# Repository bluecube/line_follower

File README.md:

Line follower v2
================

This is a robot I made to tinker with and to compete in the [Robotic Day](https://roboticday.org/) competition. (Actually the original goal was Robotic Day 2016, but stuff got delayed :) )

The design is an attempt to make a line follower with minimum effort on the hardware side and maximum versatility on the software side.

The robot body consists of a 8cm x 10cm double sided PCB, two geared N20 DC encoder motors with Pololu wheels and magnetic encoders and a few 3D printed bits.
The most important electronic components are ESP32 development board for computing power and line sensor inspired by [Ondřej Staněk's PocketBot](http://www.ostan.cz/pocketBot/), as a bonus the robot also carries an IR range sensor and MPU 6050 breakout board (accelerometer and gyro).

This repository should contain everything necessary to build and run the robot in the competition.
Let me know if you decide to build it!

This is a v2, you can also check out the [v1](https://github.com/bluecube/line_follower/tree/v1/).

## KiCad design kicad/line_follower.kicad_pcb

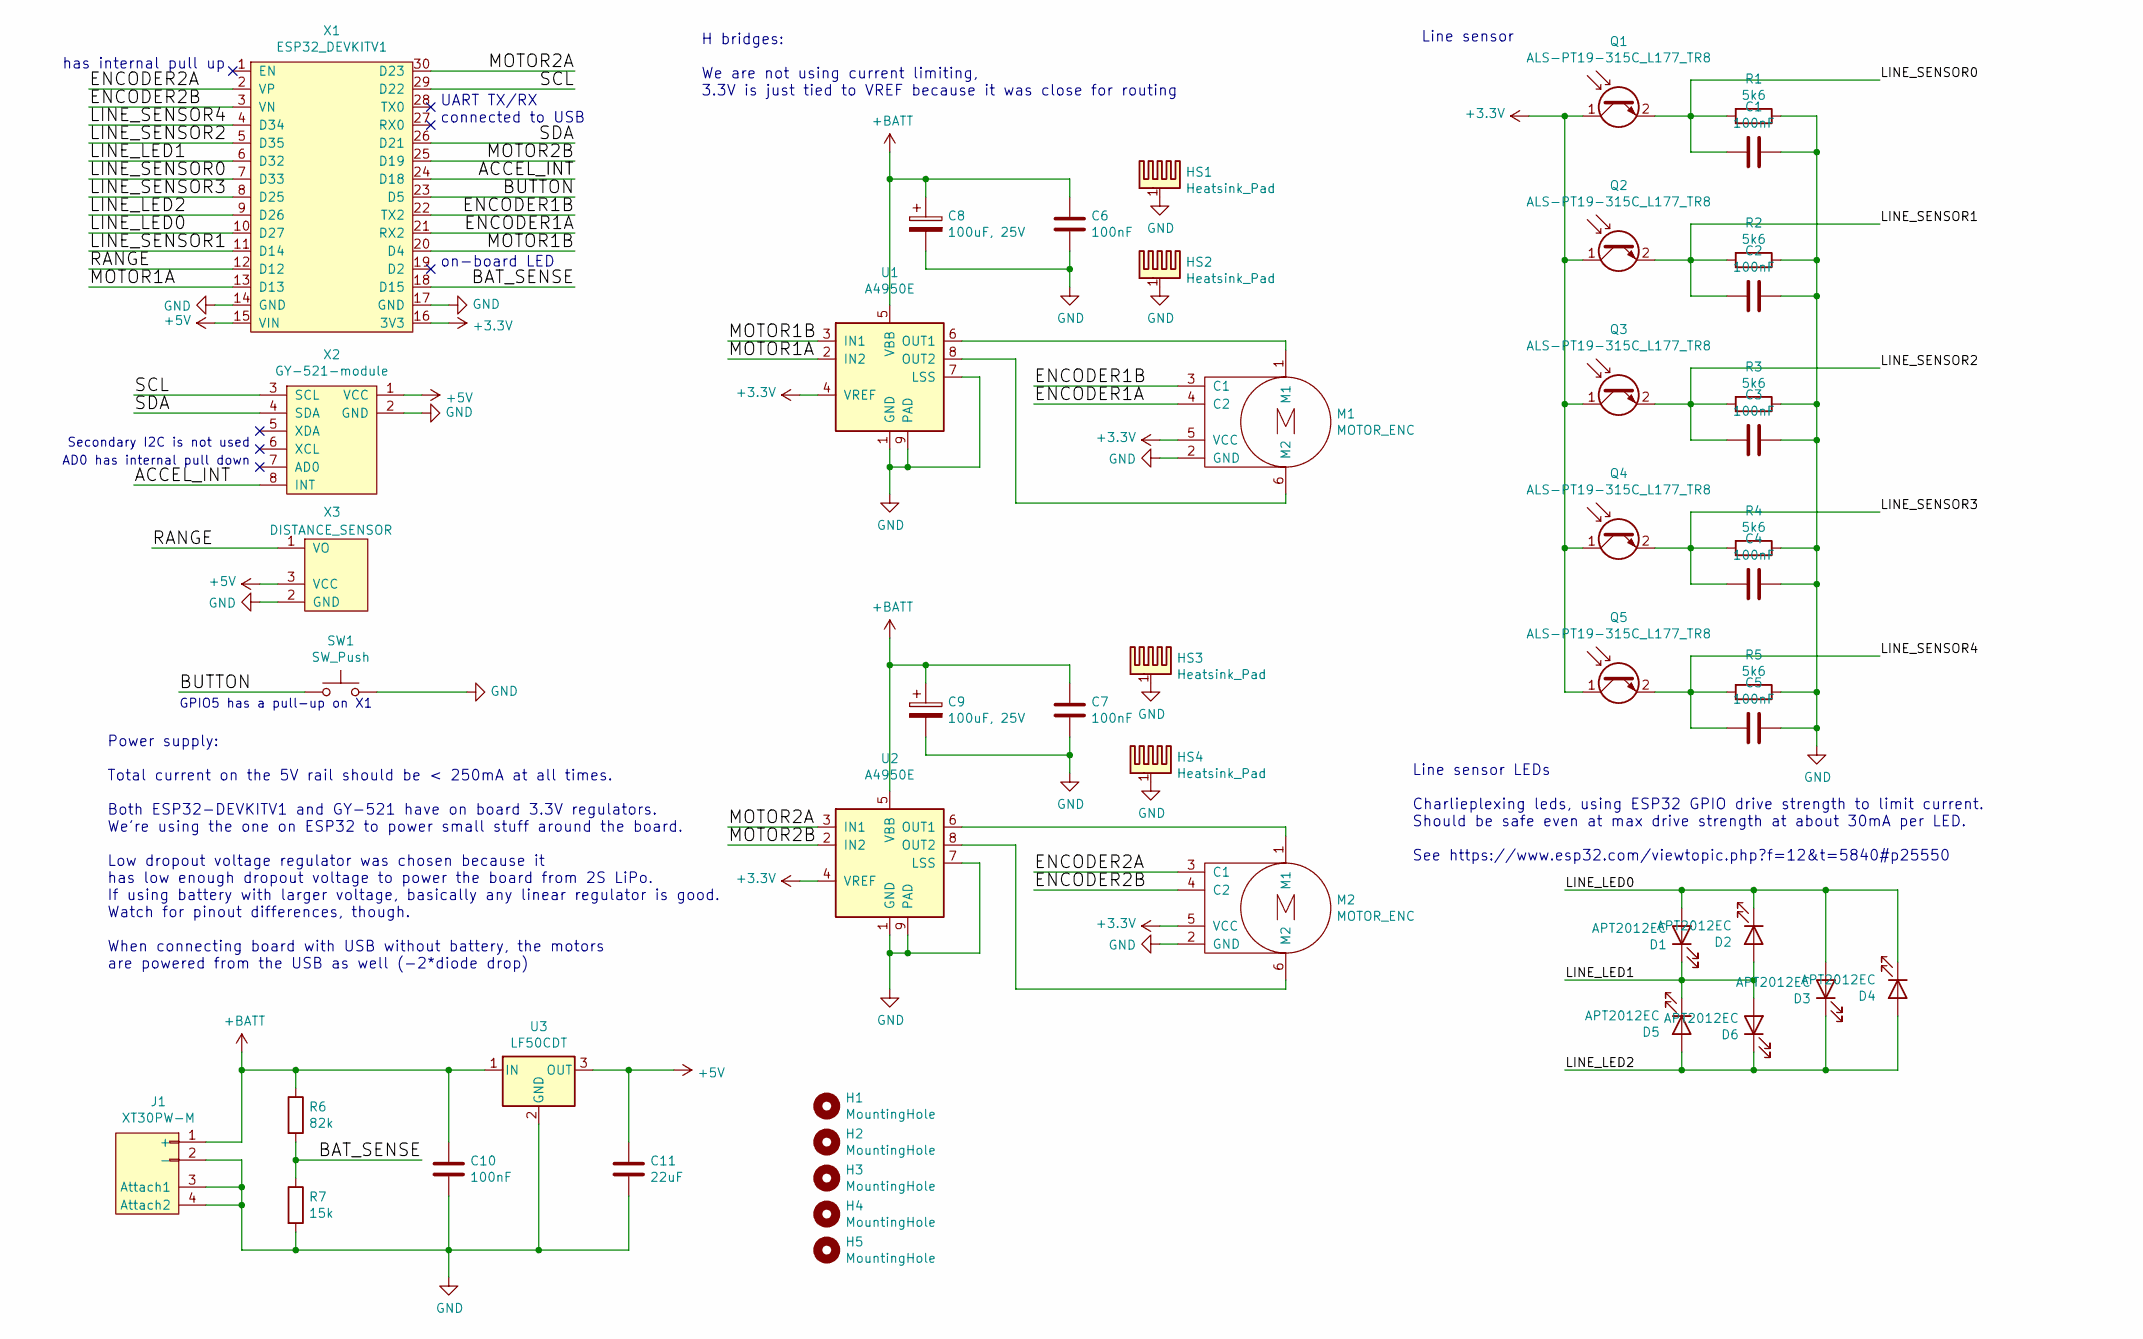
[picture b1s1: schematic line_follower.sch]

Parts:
C1, C2, C3, C4, C5, C6, C7, C10: 100nF; C_0805_2012Metric_Pad1.15x1.40mm_HandSolder
C8, C9: 100uF, 25V; CP_Elec_6.3x5.8
C11: 22uF; C_0805_2012Metric_Pad1.15x1.40mm_HandSolder
D1, D2, D3, D4, D5, D6: APT2012EC; LED_0805_2012Metric_Pad1.15x1.40mm_HandSolder
H1, H2, H3, H4, H5: MountingHole; MountingHole_3.2mm_M3
HS1, HS2, HS3, HS4: Heatsink_Pad; 3x3_thermal_vias
J1: XT30PW-M
M1, M2: MOTOR_ENC; SolderWirePad2x3_p2.54_staggered
Q1, Q2, Q3, Q4, Q5: ALS-PT19-315C_L177_TR8; phototransistor-1.7mm
R1, R2, R3, R4, R5: 5k6; R_0805_2012Metric_Pad1.15x1.40mm_HandSolder
R6: 82k; R_0805_2012Metric_Pad1.15x1.40mm_HandSolder
R7: 15k; R_0805_2012Metric_Pad1.15x1.40mm_HandSolder
SW1: SW_Push; 4.5mm_tact_switch
U1, U2: A4950E; SOIC-8-1EP_3.9x4.9mm_P1.27mm_EP2.41x3.3mm_HandSolder
U3: LF50CDT; TO-252-2
X1: ESP32_DEVKITV1
X2: GY-521-module
X3: DISTANCE_SENSOR; SolderWirePad1x3_p2.54

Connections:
+3V3: M1.5 (VCC), M2.5 (VCC), Q1.1 (C), Q2.1 (C), Q3.1 (C), Q4.1 (C), Q5.1 (C), U1.4 (VREF), U2.4 (VREF), X1.16 (3V3)
+5V: C11.1, U3.3 (OUT), X1.15 (VIN), X2.1 (VCC), X3.3 (VCC)
+BATT: C6.1, C7.1, C8.1, C9.1, C10.1, J1.1 (+), R6.1, U1.5 (VBB), U2.5 (VBB), U3.1 (IN)
/ACCEL_INT: X1.24 (D18), X2.8 (INT)
/BAT_SENSE: R6.2, R7.1, X1.18 (D15)
/BUTTON: SW1.1, X1.23 (D5)
/ENCODER1A: M1.4 (C2), X1.21 (RX2)
/ENCODER1B: M1.3 (C1), X1.22 (TX2)
/ENCODER2A: M2.3 (C1), X1.2 (VP)
/ENCODER2B: M2.4 (C2), X1.3 (VN)
/LINE_LED0: D1.2 (A), D2.1 (K), D3.2 (A), D4.1 (K), X1.10 (D27)
/LINE_LED1: D1.1 (K), D2.2 (A), D5.1 (K), D6.2 (A), X1.6 (D32)
/LINE_LED2: D3.1 (K), D4.2 (A), D5.2 (A), D6.1 (K), X1.9 (D26)
/LINE_SENSOR0: C1.2, Q1.2 (E), R1.2, X1.7 (D33)
/LINE_SENSOR1: C2.2, Q2.2 (E), R2.2, X1.11 (D14)
/LINE_SENSOR2: C3.2, Q3.2 (E), R3.2, X1.5 (D35)
/LINE_SENSOR3: C4.2, Q4.2 (E), R4.2, X1.8 (D25)
/LINE_SENSOR4: C5.2, Q5.2 (E), R5.2, X1.4 (D34)
/MOTOR1A: U1.2 (IN2), X1.13 (D13)
/MOTOR1B: U1.3 (IN1), X1.20 (D4)
/MOTOR2A: U2.3 (IN1), X1.30 (D23)
/MOTOR2B: U2.2 (IN2), X1.25 (D19)
/RANGE: X1.12 (D12), X3.1 (VO)
/SCL: X1.29 (D22), X2.3 (SCL)
/SDA: X1.26 (D21), X2.4 (SDA)
GND: C1.1, C2.1, C3.1, C4.1, C5.1, C6.2, C7.2, C8.2, C9.2, C10.2, C11.2, HS1.1, HS2.1, HS3.1, HS4.1, J1.2 (-), J1.3 (Attach1), J1.4 (Attach2), M1.2 (GND), M2.2 (GND), R1.1, R2.1, R3.1, R4.1, R5.1, R7.2, SW1.2, U1.1 (GND), U1.7 (LSS), U1.9 (PAD), U2.1 (GND), U2.7 (LSS), U2.9 (PAD), U3.2 (GND), X1.14 (GND), X1.17 (GND), X2.2 (GND), X3.2 (GND)
unnamed: M1.1 (M1), U1.6 (OUT1)
unnamed: M1.6 (M2), U1.8 (OUT2)
unnamed: M2.1 (M1), U2.6 (OUT1)
unnamed: M2.6 (M2), U2.8 (OUT2)

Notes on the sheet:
Power supply: Total current on the 5V rail should be < 250mA at all times. Both ESP32-DEVKITV1 and GY-521 have on board 3.3V regulators. We're using the one on ESP32 to power small stuff around the board. Low dropout voltage regulator was chosen because it has low enough dropout voltage to power th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
UART TX/RX connected to USB
on-board LED
AD0 has internal pull down
has internal pull up
Secondary I2C is not used
H bridges: We are not using current limiting, 3.3V is just tied to VREF because it was close for routing
Line sensor LEDs Charlieplexing leds, using ESP32 GPIO drive strength to limit current. Should be safe even at max drive strength at about 30mA per LED. See https://www.esp32.com/viewtopic.php?f=12&t=5840#p25550
Line sensor
GPIO5 has a pull-up on X1

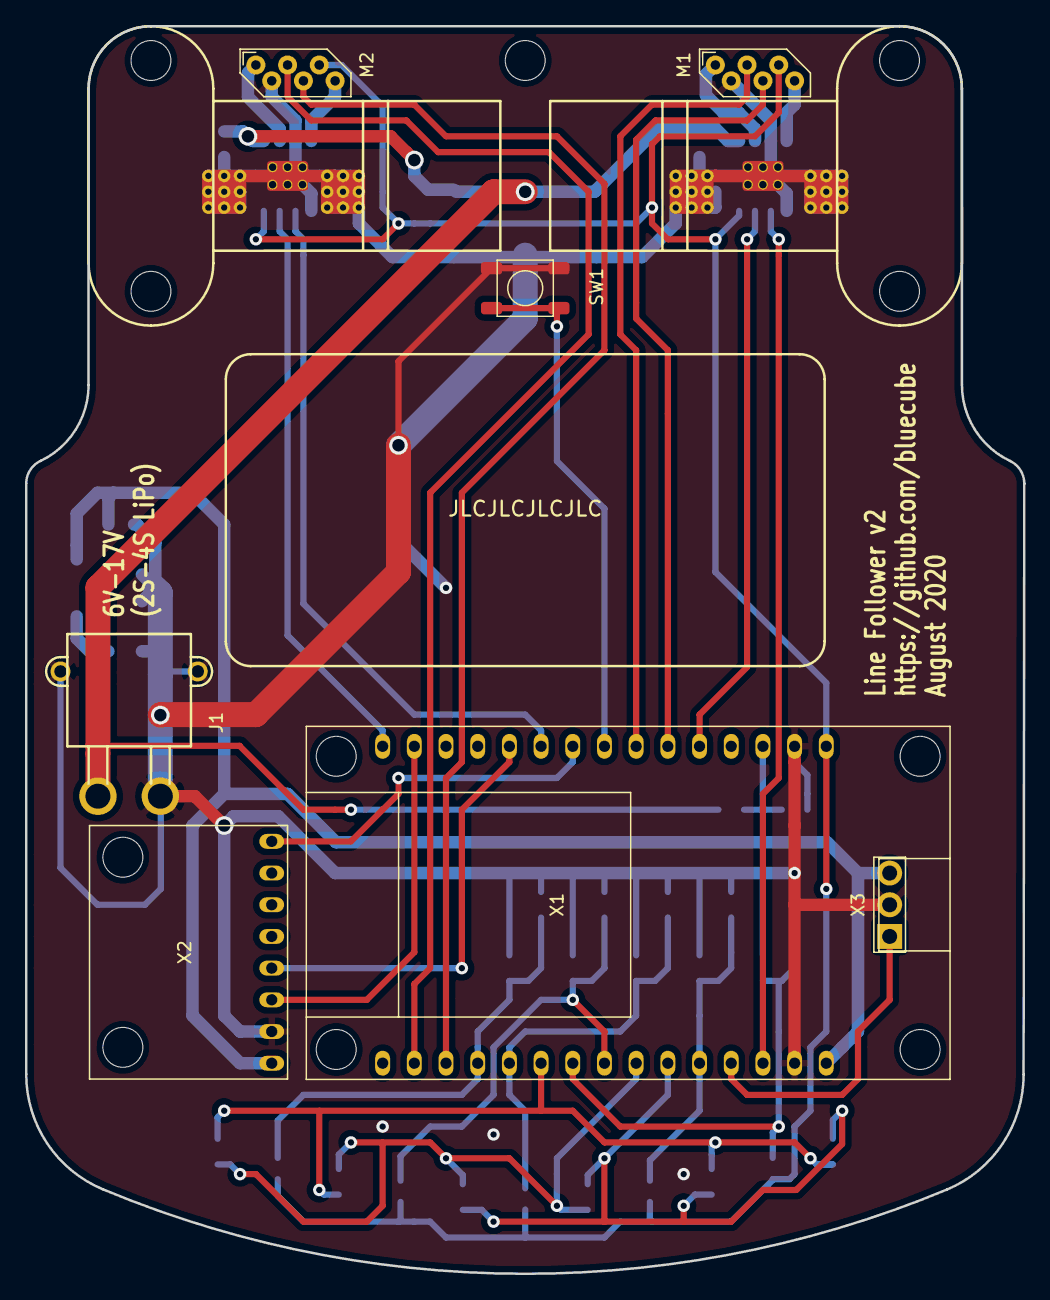
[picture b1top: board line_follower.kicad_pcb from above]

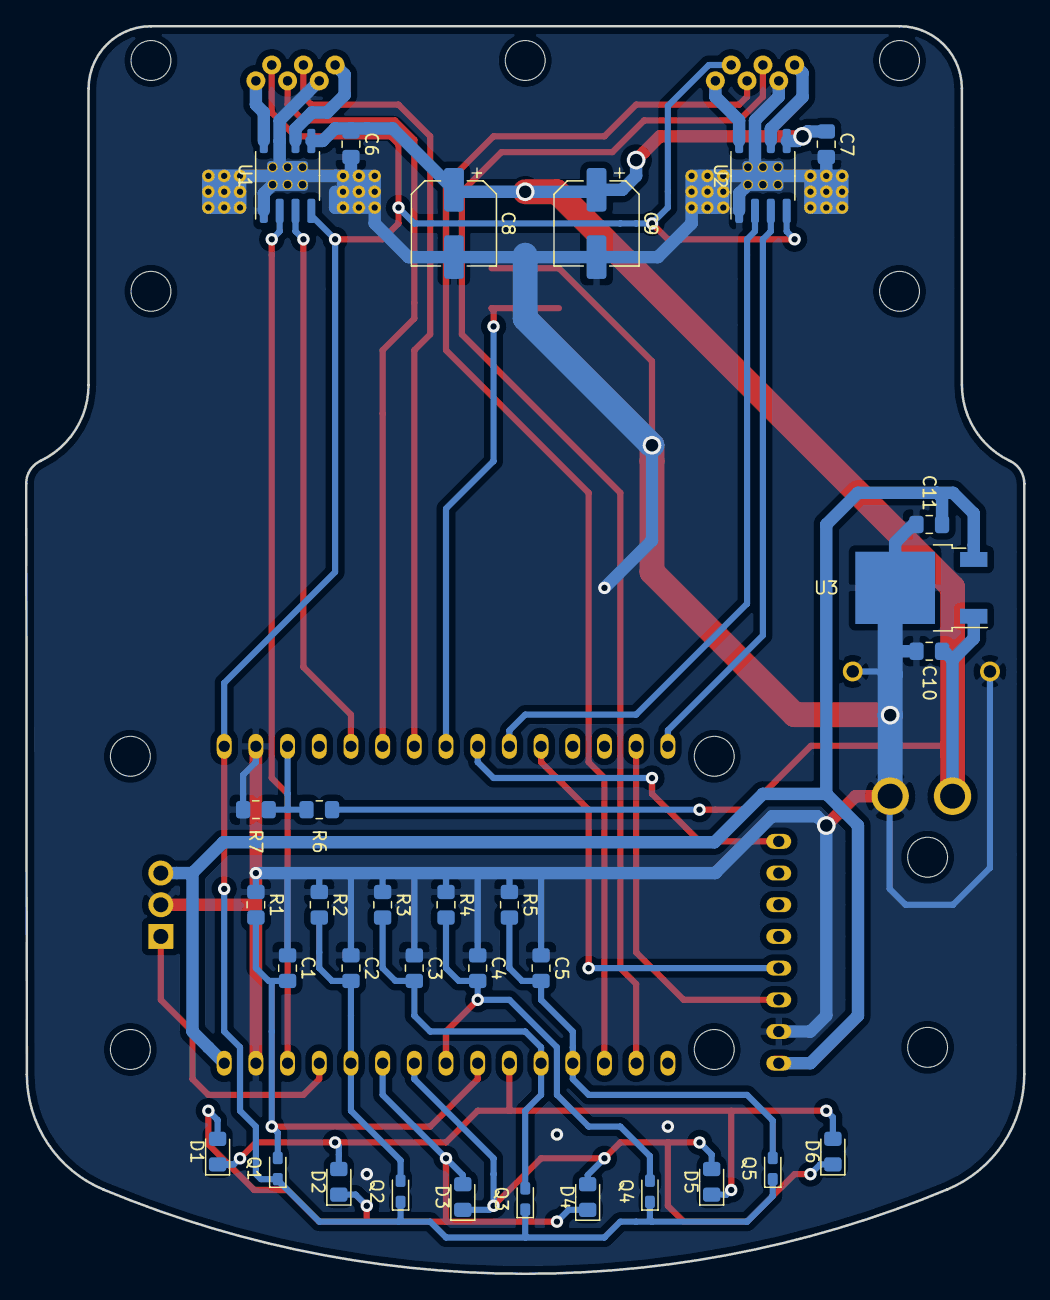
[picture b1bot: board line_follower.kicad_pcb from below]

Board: 2 copper layers, 80.0 x 100.0 mm, 48 parts (32 on the bottom side), 30 nets.

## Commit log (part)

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2016-04-03 Initial commit.
    3D sketch in solidworks and almost finished board.
2016-04-16 Fixes before sending the board for fab.
2016-05-12 Got rid of old versions of model.
2016-05-28 Testing arena design.
2016-05-29 Added missing connections to the board.
2016-06-27 Updated the testing map to 1x1.5m format.
2016-06-29 Updated testing map
2016-07-03 One more change of the testing map.
    I should really be doing more useful stuff :-)
2016-10-12 Blink zinc example that compiles
2016-10-12 Very rough (non compilable by far) idea of top level code separation
2017-02-13 More realistic wheel shape
2017-02-13 3D printable distance sensor bracket, front ball and motor brackets.
2017-02-13 Removed unused solidworks parts
2017-05-28 Working blink example
2018-12-16 Cleaned up old attempts
2019-01-06 Crosstool configuration for building the toolchain.
2019-01-06 Cleaning up the remaining pieces of rust coniguration.
2019-04-14 Starting with C++ project
2019-04-15 Larson scanner hello world with arduino.
2019-04-27 Settled on using Arduino with platformio.
2019-04-28 Playing with LEDs
2019-04-28 Added comment.
2019-04-28 Very simple reading of analog values.
2019-05-18 Carrying case first draft
2019-05-19 Short introduction text for Robotic Day 2019
2019-05-19 Robotic day photos.
2019-05-19 Fixed values of line sensor divider resistors.
2019-05-19 Started a list of hardware bugs.
2019-05-19 Some work done on the carrying box.
2019-05-19 Small change in robotic day introduction
2019-05-19 Readme improvements.
2019-05-20 Added a github link to short introduction file
2019-05-20 Create LICENSE
2019-05-21 Added jupyter notebook containing experiments with line detection cross-corelation kernels
2019-05-21 Line sensor reacts now.
2019-05-21 One more (minor) hardware bug.
2019-05-21 Prepared testing map for printing
2019-05-26 Carrying box ready for printing.
2019-05-26 Cleaning up line sensor code, using at least a few parallel ADC reads.
2019-05-27 Fixing uninitialized ADC instance after move to singleton.
2019-05-28 Line detection working.
2019-05-29 Simplified line detector.
2019-05-29 Renamed LfHal to RobotHal
2019-05-30 Debounced button input.
2019-05-31 Cleaning up Hal, simplified the replacability.
2019-06-01 Fixed changing motor directions (analogWrite and digitealWrite don't mix)
2019-06-01 State machine with basic line following code
2019-06-01 Added bootup state.
2019-06-01 Setting loop period
2019-06-01 Somehow working line following
2019-06-01 Fixing missing enum members in switch
2019-06-01 Rudimentary battery voltage monitoring
2019-06-01 Still fiddling with parameters
2019-06-02 Smoother line finding.
2020-04-25 Schematic for V2 mostly complete, time to work on the board.
2020-04-26 Removed obsolete solidworks models
2020-04-26 Updated gitignore
2020-04-26 You'll have to google for the datasheets yourself.
2020-04-26 Rough layout of the new board
2020-04-29 Modelled a bunch of new parts for the robot
2020-04-29 Decided to not use the encoder board on the motors, schematic tweaks and start of layout
2020-05-19 Motor encoder boards are back, more layout work
2020-05-20 Another quarter-afternoon of layout
2020-05-22 Everything is connected on the board, but more work remains
2020-05-22 Layout complete, now a day or two for it to sink in and find more errors.
2020-06-04 started working on kicad version of the board
2020-07-01 Board: Almost complete schematic, rough layout of pcb
2020-07-01 WIP mechanical design in F360
2020-07-23 Getting there with the PCB design.
2020-07-24 Updated sensor components position export
2020-08-02 Board done except for the motor mounts
2020-08-02 Small PCB tweaks
2020-08-02 Placed motor mounting holes and silkscreen outlines.
    Board done for now.
2020-08-09 Untangled routing at the front of the robot a bit, moved battery location
2020-08-10 board: A bit more tweaking
2020-08-10 board: Moving silkscreen labels
2020-08-13 board: Manually fixed the outline to make step exporter happy
2020-08-15 Ignoring kicad autosave files.
2020-08-15 mechanical: WIP 3d printed parts and robot layout
    Front top and bottom pieces are ready, motor mounts and deck are missing
2020-08-26 board: Added model for microswitch
2020-08-26 board: Some silkscreen change ...
2020-08-26 schematic: Fixing DRC warnings
2020-08-26 schematic: Removed comment
2020-08-26 board: Small tweaks + updating to match previous changes.
2020-08-26 board: Gerber files, sent for manufacture
2020-10-02 CAD model ready for 3D printing
2020-10-02 Added Step export of the CAD model
2020-10-06 mechanical: Updated based experimental prints.
2020-10-14 schematic: Modified power supply LDO because of availability at Mouser.
2020-10-14 mechanical: More updates, refreshed exports
2020-10-15 mechanical: Cleanup + added readme
2020-11-08 Set theme jekyll-theme-cayman
2020-11-12 Exporter script for the Fusion360 design
2020-11-12 schematic: Changed the 5V regulator again
    the previous one had wrong pinout
2020-11-12 mechanical: Printability improvements and smaller tweaks
2020-11-13 Renamed kicad exports directory
2020-12-06 Updated platformio to work with ESP32.
2020-12-06 Removed Arduino calls from code except HAL
2020-12-06 Silencing compiler warnings
2020-12-07 RobotHal: Got rid of Arduino remnants
2020-12-07 RobotHal: New pin assignments
2020-12-07 RobotHal: Singleton stuff
2020-12-07 Formating
2020-12-08 Using C++17
2020-12-08 Blinking LEDs through RobotHal
2020-12-10 Removed the obsolete eagle project
2020-12-10 Removed obsolete solidworks designs
2020-12-10 Updated README to reflect the branch renaming
2020-12-10 Fixed image path in readme
2020-12-10 Line sensor buffer definitions.
2020-12-12 Naming convention
2020-12-12 Got rid of time types for now (will be replaced by std::chrono later)
2020-12-12 WIP line sensor reading
2020-12-12 Line sensor kind of working
2020-12-20 Reading motor encoders
2020-12-20 Printf!
2020-12-22 Moved RobotHal to a separate directory
2020-12-22 Coding style change for encoder configuration
2020-12-23 idf_util needed to be moved as well
2020-12-23 Added Vector3D class
2020-12-25 Initial non-working IMU code
2020-12-26 Refactored Line sensor to a separate class under HAL
2020-12-26 IMU HAL component uses static methods rather than HAL reference.
2020-12-26 More reasonable naming scheme for HAL components
2020-12-26 Refactored motor control to separate HAL component
2020-12-26 Utility for checking ESP-IDF error codes
2020-12-26 Debug print tweaks
2020-12-27 HAL: Reading battery voltage
2020-12-27 Removed commented block of old code from main
2020-12-27 HAL: Line sensor LED pins should start as disabled
2020-12-27 HAL: Setting motor PWM
2020-12-27 HAL: Fixing I2C register reading code
2020-12-27 HAL: One more printf during init
2020-12-27 HAL/Mpu6050: Checking connection, attempting to wake from sleep mode
    Connection works, but accelerometer and gyro still read as zeros
2020-12-31 Removed old documentation related to v1
2020-12-31 Moved the line sensor experiments to jupyter directory
2021-01-03 Schematic of the planned balancing algorithm.
2021-01-08 HAL: Motor beeping
2021-02-07 Ignoring jupyter checkpoints
2021-02-07 HAL: Compilation fix for latest ESP-IDF
2021-02-07 HAL: Number of line sensor LEDS must be public
2021-02-07 Preparing PID controller helper for units
2021-02-07 Ignoring Fusion360 plugin junk
2023-01-17 Renamed deprecated config from platformio.ini
2023-02-18 Untested ADC library update.
2023-03-01 Partially converted motor module of HAL to use the new libraries
2023-03-01 Removed motor beeping functionality
2023-03-03 Finalized HAL for motors
2023-03-03 Tweaking shortcuts in makefile
2023-03-05 Ignore warnings from missing field initializers
2023-03-05 Selectable serial port in Makefile
2023-03-05 C++ wrapper for ESP32 high resolution timer
2023-03-05 Using ESP_ERROR_CHECK instead of HAL_CHECK
2023-03-06 Cleaned up includes
2023-03-29 Renamed EspTimer header file, added Clock to Hal
2023-03-29 Removed old button event enum from Hal
2023-03-29 Added Hal sub-component types to typedef, to allow accessing compile time constants
2023-03-29 Fixed a typo
2023-04-10 Renaming Pid to PidController.
2023-04-10 Removed parameters already defined elsewhere
2023-04-10 Remove obsolete commented code from main
2023-04-10 hal: Refactored to a PIO library
2023-04-10 Old state machine almost removed
    We keep the files around to rescue some of the line following code
2023-04-10 Removing old code
2023-04-10 Moved most of functionality to a library
    for easier unit testing
2023-04-18 Unit tesing for the C++ code
2023-04-18 Encoder observer Kalman filter
    Seems to work, but not so great performance yet
2023-04-27 Don't optimize tests at all
2023-04-28 Removed unused code
2023-04-29 Borrowed CircularBuffer from bluecube/tablog
2023-05-04 New version of encoder observer
    uses line fitting of velocitites instead of Kalman filter, adaptive window size.
2023-05-11 Texts for Robotic Day 2023
2023-05-27 HAL abstraction for running periodic tasks
2023-05-27 Initial version of motor velocity controller
2023-05-27 Tweaks in encoder observer
2023-05-28 Create instructions.md
    First try to collect notes about building the robot.
2023-06-12 Measured rangefinder distances for calibration, not finished yet
2023-06-15 Skeleton of rangefinder HAL API.
2023-06-18 Added accessing const data to periodic task
2023-06-18 Reading out current velocity from motor velocity controler
2023-06-27 Changed motors to ones with 1:30 gear ratio
2026-04-23 Setting up LSP in helix
2026-04-23 Starting rust rewrite, Motors work.
2026-04-24 Button handling
2026-04-27 Line sensor LED control
2026-04-27 Updated CLAUDE.md
2026-04-28 Line sensor ADC reading
2026-05-01 Simplified line sensor HAL code
2026-05-01 HAL: Formating button code
2026-05-01 Ranged integers in LineSensor API
2026-05-04 Refactoed Rust rewrite to better separate HAL
2026-05-04 Line detection algorithm
2026-05-04 Moved C++ version into `old-c++-firmware`
2026-05-04 Fixed comments about ADC inversion
2026-05-04 CLAUDE.md tweak
2026-05-04 Reading the battery voltage and WIP reading the distance sensor
2026-05-05 Distance sensor calibration + updated calibration binaries
2026-05-07 Onboard LED
2026-05-08 Added a constant for rough maximum motor speed.
2026-05-09 Mysterious style tweak to line detection
2026-05-11 Velocity controller with preliminary PID tuning
2026-05-11 CLAUDE.md update
2026-05-16 Ignoring pycache
    That should never have been commited..
2026-05-24 Comment changes
2026-05-24 Moving to Embassy for async tasks
2026-05-24 Minor refactoring of set_led
2026-05-24 Updated dependencies
2026-05-25 Moved velocity controller to use embassy_time units instead of raw microseconds
2026-05-27 Making button code async
2026-05-27 Fixing a line sensor bug
    This likely happened when an update of esp-hal fixed the inversion bug
2026-05-27 Async line sensor readout
2026-06-01 Listing all that is wrong with the design and needs to be worked around
2026-06-01 Python client for bluetooth logs
2026-06-01 Removed arrayvec dependency, using heapless::Vec instead
2026-06-05 New HAL tester binary, removed obsolete motor_test.
2026-06-05 Fixing button EMI issues in software only...
2026-06-05 Line detection now exports the PositionT type to communicate the detection value scale.
2026-06-05 Improved HAL test
2026-06-06 Decreased line detection sensitivity, updated tests
2026-06-06 METERS_PER_TICK changed from f64 to f32
2026-06-08 Line following, almost working
2026-06-09 Faster line sensor reading
2026-06-09 Constants describing the hardware in lf-hal-types
2026-06-09 Mandelbrot set benchmark
2026-06-09 Got rid of the old firmware
2026-06-10 Moving line detection and velocity controlller to use `fixed`
2026-06-10 Making clippy happy
2026-06-11 Playing with line following code
2026-06-13 Refactored HAL to have battery and range in separate structs
2026-06-13 Restructured main to use fixed 100Hz update rate, button checking in parallel withh line following
